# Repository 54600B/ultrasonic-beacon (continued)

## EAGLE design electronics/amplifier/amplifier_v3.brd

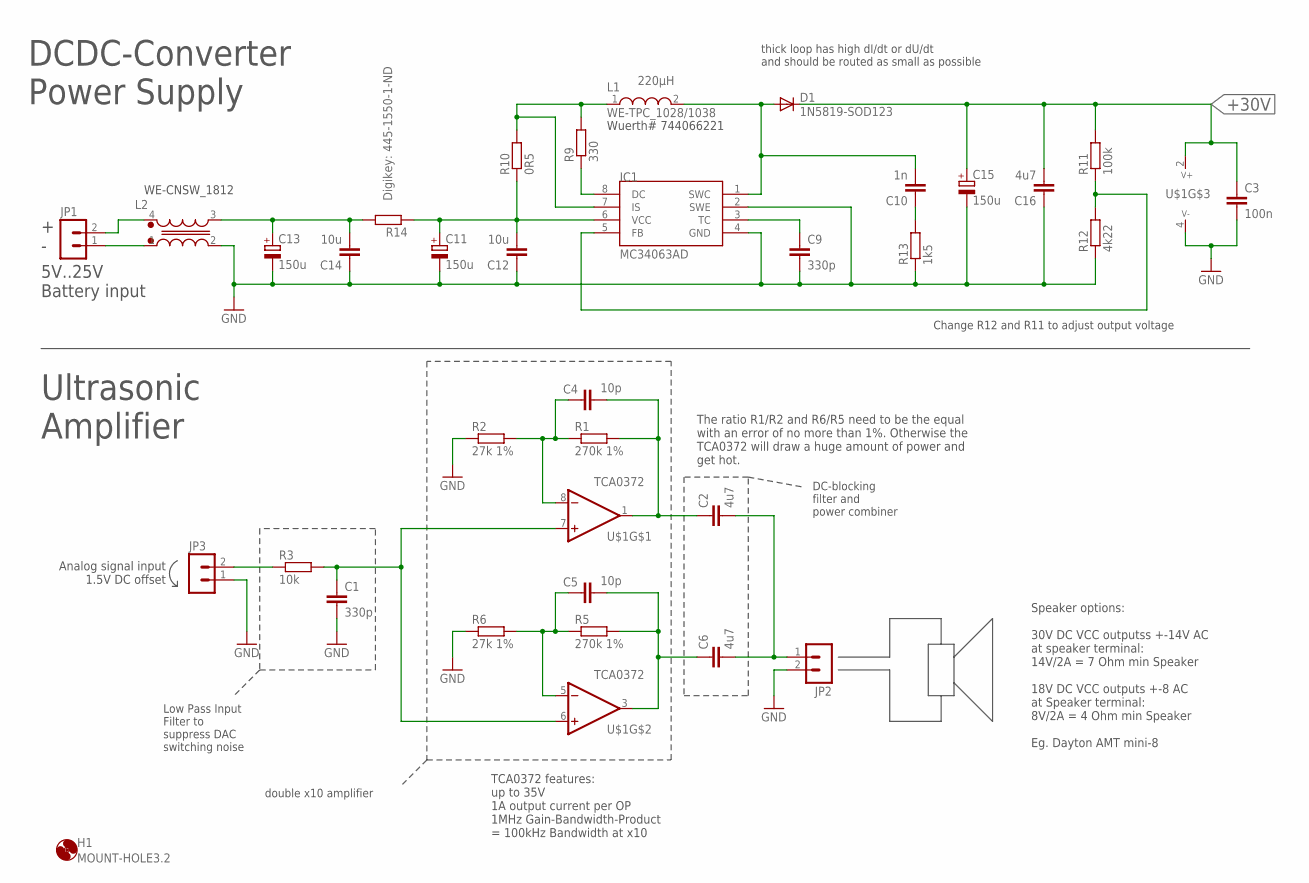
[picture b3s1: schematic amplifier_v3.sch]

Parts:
C1, C9: 330p; C0603
C2, C6, C16: 4u7; C0805
C3: 100n; C0603
C4, C5: 10p; C0603
C10: 1n; C0603
C11, C13, C15: 150u; E3,5-8
C12, C14: 10u; C0805
D1: 1N5819-SOD123; SOD123
H1: MOUNT-HOLE3.2; 3,2
IC1: MC34063AD; SOIC8
JP1, JP2, JP3: PSS_2G; 22-23-2021
L1: WE-TPC_1028/1038
L2: WE-CNSW_1812
R1, R5: 270k 1%; R0603
R2, R6: 27k 1%; R0603
R3: 10k; R0603
R9: 330; R0603
R10: 0R5; R0603
R11: 100k; R0603
R12: 4k22; R0603
R13: 1k5; R0603
R14: Digikey: 445-1550-1-ND; R0603
U$1: TCA0372; DIL08

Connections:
+30V: C3.1, C15.+, C16.2, D1.C, R11.2, U$1.2 (V+)
GND: C1.2, C3.2, C9.2, C11.-, C12.1, C13.-, C14.1, C15.-, C16.1, IC1.2 (SWE), IC1.4 (GND), JP2.2, JP3.1, L2.2 (3), R2.1, R6.1, R12.1, R13.1, U$1.4 (V-)
unnamed: JP3.2, R3.1
unnamed: C2.1, C4.2, R1.2, U$1.1 (OUT)
unnamed: C2.2, C6.2, JP2.1
unnamed: C4.1, R1.1, R2.2, U$1.8 (-IN)
unnamed: C1.1, R3.2, U$1.6 (+IN), U$1.7 (+IN)
unnamed: C5.2, C6.1, R5.2, U$1.3 (OUT)
unnamed: C5.1, R5.1, R6.2, U$1.5 (-IN)
unnamed: JP1.1, L2.1 (4)
unnamed: JP1.2, L2.4 (1)
unnamed: IC1.8 (DC), R9.1
unnamed: IC1.7 (IS), L1.1, R9.2, R10.2
unnamed: IC1.5 (FB), R11.1, R12.2
unnamed: C9.1, IC1.3 (TC)
unnamed: C10.1, R13.2
unnamed: C11.+, C12.2, IC1.6 (VCC), R10.1, R14.1
unnamed: C13.+, C14.2, L2.3 (2), R14.2
SWN: C10.2, D1.A, IC1.1 (SWC), L1.2

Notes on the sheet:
Wuerth# 744066221
The ratio R1/R2 and R6/R5 need to be the equal with an error of no more than 1%. Otherwise the TCA0372 will draw a huge amount of power and get hot.
Analog signal input 1.5V DC offset
TCA0372 features: up to 35V 1A output current per OP 1MHz Gain-Bandwidth-Product = 100kHz Bandwidth at x10
Speaker options: 30V DC VCC outputss +-14V AC at speaker terminal: 14V/2A = 7 Ohm min Speaker 18V DC VCC outputs +-8 AC at Speaker terminal: 8V/2A = 4 Ohm min Speaker Eg. Dayton AMT mini-8
WE-CNSW_1812
DCDC-Converter Power Supply
Ultrasonic Amplifier
5V..25V Battery input
thick loop has high dI/dt or dU/dt and should be routed as small as possible
Change R12 and R11 to adjust output voltage
Low Pass Input Filter to suppress DAC switching noise
DC-blocking filter and power combiner
double x10 amplifier
220µH

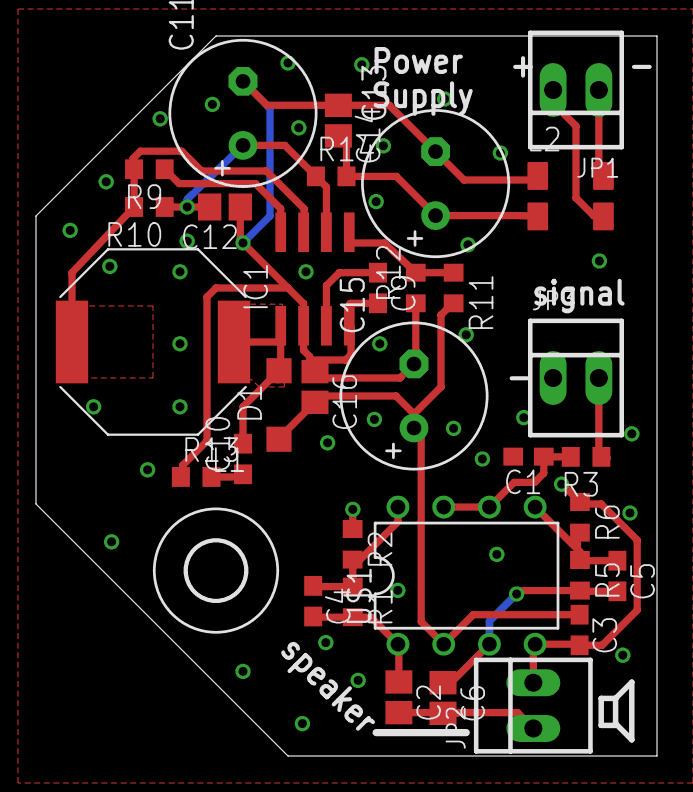
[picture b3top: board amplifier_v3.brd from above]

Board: 2 copper layers, 34.5 x 40.0 mm, 34 parts (0 on the bottom side), 19 nets.

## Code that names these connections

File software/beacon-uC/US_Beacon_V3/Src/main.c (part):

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enum BoardBehaviour boardBehaviour = SLAVE_SENDER_1; // change this constant to compile the code for different beacons on pcb version V1, in V2, V3 and V3_NRF the behaviour is set by the is switch

enum Signal {
	MIC1 = 0, MIC2 = 1, MIC3 = 2, MIC4 = 3, IR = 4
};

enum SynchronizationSource {
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	TIM5->CR1 = TIM_CR1_CEN;

	/*
	//Timer3 is used to generate a PWM on PC9 which enables the LEDs of the IR-lighthouse
	RCC->APB1ENR |= RCC_APB1ENR_TIM3EN;
	TIM3->CCER = TIM_CCER_CC4E;
	TIM3->CR2 = TIM_CCMR2_OC4M_2 | TIM_CCMR2_OC4M_1 | TIM_CCMR2_OC4M_0
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
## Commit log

2018-07-22 as presented at rwth TI-institute
2018-10-21 microphone amplifier board
2018-11-11 +documentation V1.0
2019-01-06 added checkbox in matlab_playground_gui to enable waveform debug mode
